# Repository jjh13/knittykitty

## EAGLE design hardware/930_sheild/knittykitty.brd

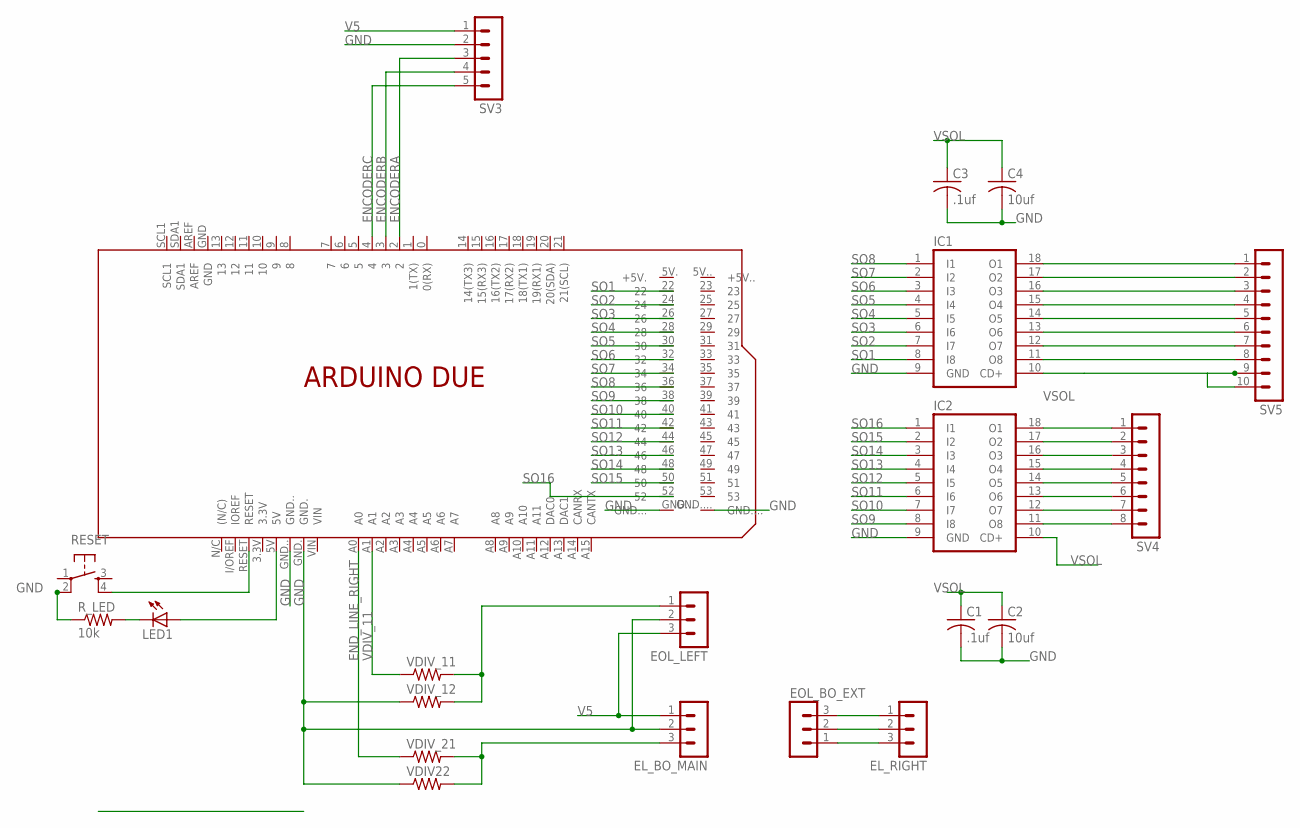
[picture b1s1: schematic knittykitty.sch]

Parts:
C1, C3: .1uf; C1206
C2, C4: 10uf; C1206
EL_BO_MAIN: MA03-1
EL_RIGHT: MA03-1
EOL_BO_EXT: MA03-1
EOL_LEFT: MA03-1
IC1, IC2: ULN2803ASO; SO18W
LED1: LEDSMT1206; 1206
PCB1: ARDUINO_DUE_MIN
RESET: 6MM_SWITCH6MM_SWITCH; 6MM_SWITCH
R_LED: 10k; R1206FAB
SV3: MA05-1
SV4: MA08-1
SV5: MA10-1
VDIV22: R-US_R1206; R1206
VDIV_11, VDIV_12, VDIV_21: R-US_R1206; R1206

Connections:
EL_BO_EXT: EL_RIGHT.1, EOL_BO_EXT.3
ENCODERA: PCB1.2, SV3.3
ENCODERB: PCB1.3, SV3.4
ENCODERC: PCB1.4, SV3.5
END_LINE_RIGHT: PCB1.A0, VDIV_21.1
GND: C1.2, C2.2, C3.2, C4.2, EL_BO_MAIN.2, EOL_LEFT.2, IC1.9 (GND), IC2.9 (GND), PCB1.GND., PCB1.GND.., RESET.2 (P1), R_LED.1, SV3.2, VDIV22.1, VDIV_12.1
unnamed: PCB1.RESET, RESET.4 (S1)
unnamed: IC1.18 (O1), SV5.1
unnamed: IC2.18 (O1), SV4.1
unnamed: LED1.C, R_LED.2
unnamed: IC1.17 (O2), SV5.2
unnamed: IC1.16 (O3), SV5.3
unnamed: IC1.15 (O4), SV5.4
unnamed: IC1.14 (O5), SV5.5
unnamed: IC1.13 (O6), SV5.6
unnamed: IC1.12 (O7), SV5.7
unnamed: IC1.11 (O8), SV5.8
unnamed: IC2.17 (O2), SV4.2
unnamed: IC2.16 (O3), SV4.3
unnamed: IC2.15 (O4), SV4.4
unnamed: IC2.14 (O5), SV4.5
unnamed: IC2.13 (O6), SV4.6
unnamed: IC2.12 (O7), SV4.7
unnamed: IC2.11 (O8), SV4.8
unnamed: EOL_LEFT.1, VDIV_11.2, VDIV_12.2
unnamed: EL_BO_MAIN.3, VDIV22.2, VDIV_21.2
unnamed: EL_RIGHT.2, EOL_BO_EXT.2
unnamed: EL_RIGHT.3, EOL_BO_EXT.1
SO1: IC1.8 (I8), PCB1.22
SO2: IC1.7 (I7), PCB1.24
SO3: IC1.6 (I6), PCB1.26
SO4: IC1.5 (I5), PCB1.28
SO5: IC1.4 (I4), PCB1.30
SO6: IC1.3 (I3), PCB1.32
SO7: IC1.2 (I2), PCB1.34
SO8: IC1.1 (I1), PCB1.36
SO9: IC2.8 (I8), PCB1.38
SO10: IC2.7 (I7), PCB1.40
SO11: IC2.6 (I6), PCB1.42
SO12: IC2.5 (I5), PCB1.44
SO13: IC2.4 (I4), PCB1.46
SO14: IC2.3 (I3), PCB1.48
SO15: IC2.2 (I2), PCB1.50
SO16: IC2.1 (I1), PCB1.52
V5: EL_BO_MAIN.1, EOL_LEFT.3, LED1.A, PCB1.5V, SV3.1
VDIV_11: PCB1.A1, VDIV_11.1
VSOL: C1.1, C2.1, C3.1, C4.1, IC1.10 (CD+), IC2.10 (CD+), SV5.9, SV5.10

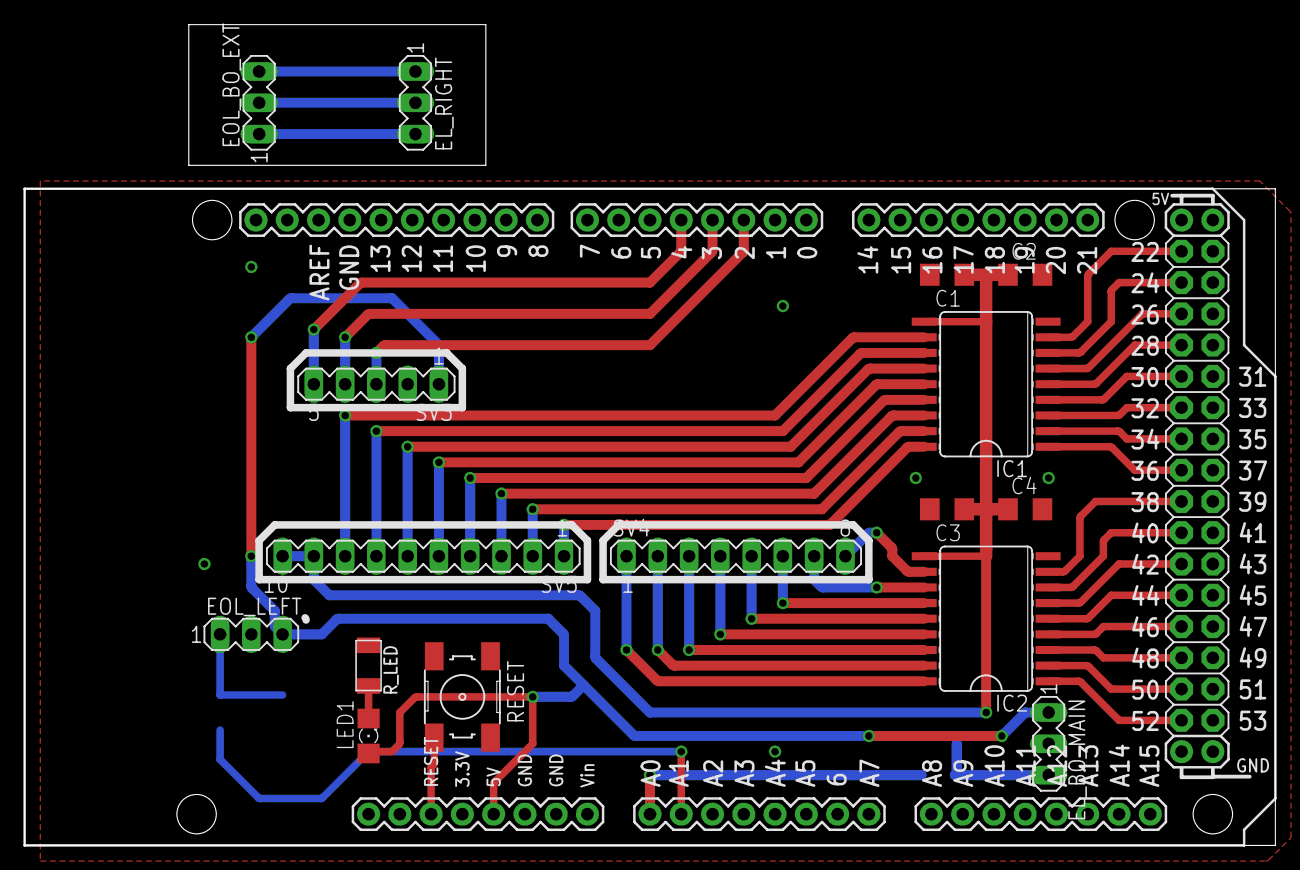
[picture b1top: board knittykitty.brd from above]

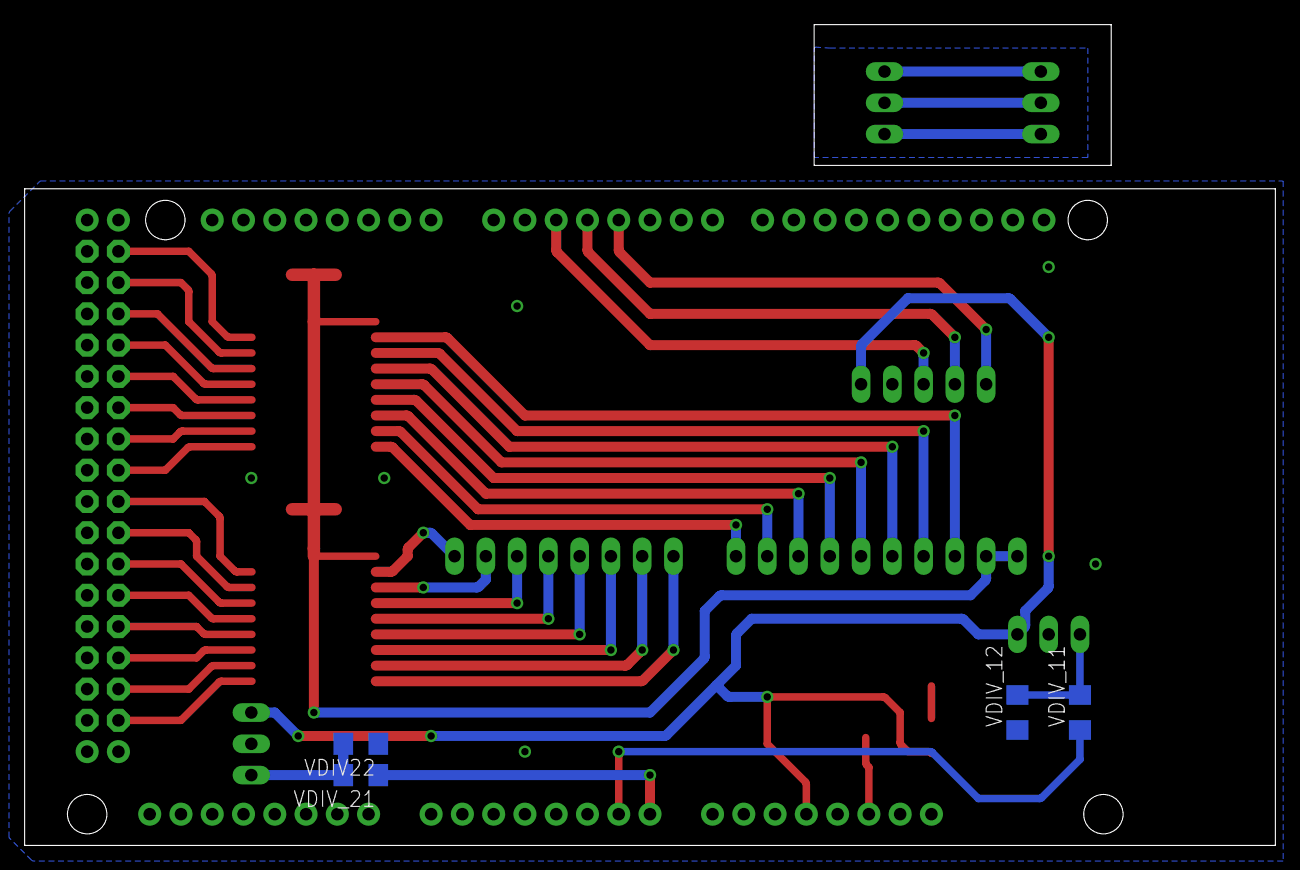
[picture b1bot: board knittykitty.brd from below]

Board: 2 copper layers, 101.6 x 66.7 mm, 21 parts (4 on the bottom side), 47 nets.

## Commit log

2016-10-24 Adding initial firmware files
2016-10-24 Adding eagle design files for 930e
2016-10-28 Updating with fixed state machine and proper pin-mappings for solenoid array
2016-11-09 Updating firmware with proper pin mappings
2016-11-30 Working hacky values for knit carriage
2016-12-06 Updating and refactoring firmware
2017-02-25 Adding slightly new version with updated timing
2017-03-01 Added pattern buffering for fw
